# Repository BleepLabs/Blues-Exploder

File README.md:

The Jon Spencer Blues Exploder

Back in 2012 I had the great pleasure of working with Jon Spencer to make this weird thing.
http://bleeplabs.com/exploder/

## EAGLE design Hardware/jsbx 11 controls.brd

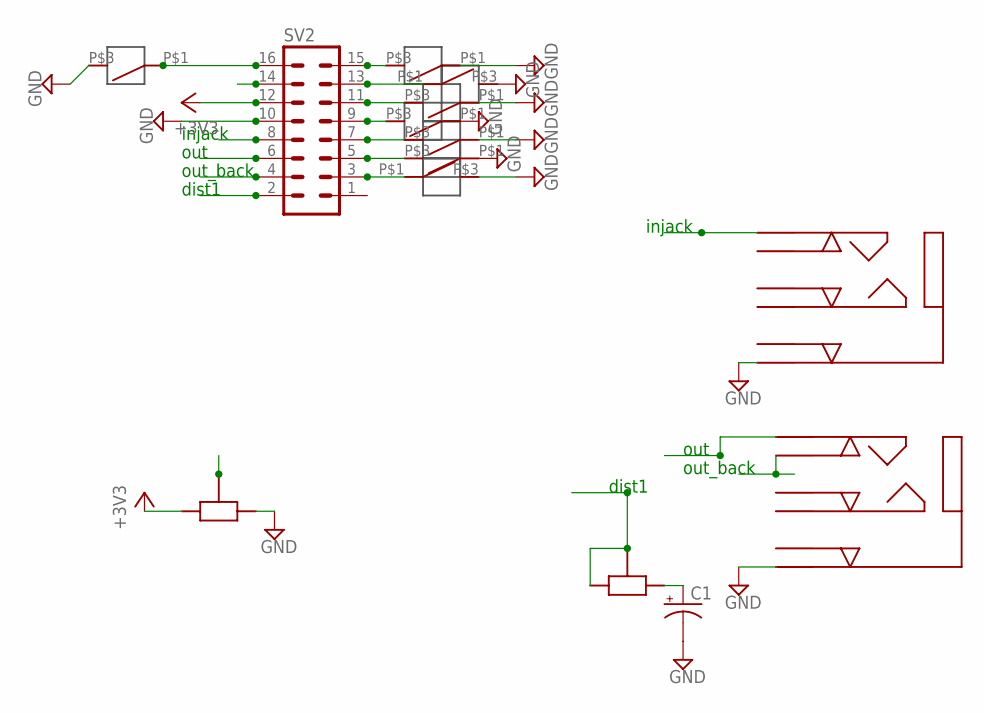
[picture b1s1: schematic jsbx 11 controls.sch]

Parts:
B1, B2, B3, B4, B5, B6, B7, B8: SPDT_TOPHAT
C1: CPOL-USE2.5-7; E2,5-7
SV2: MA08-2
U$12, U$13: POT
U$14, U$15: 1/4STEREO

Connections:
+3V3: SV2.12, U$12.P$1
B1: SV2.14, U$12.P$2
DIST1: SV2.2, U$13.P$1, U$13.P$2
GND: B1.P$1, B1.P$2, B2.P$3, B2.P$4, B3.P$1, B3.P$2, B4.P$1, B4.P$2, B5.P$3, B5.P$4, B6.P$1, B6.P$2, B7.P$1, B7.P$2, B8.P$3, B8.P$4, C1.-, SV2.10, U$12.P$3, U$14.P$1, U$15.P$1
GPOT: B4.P$3, B4.P$4, SV2.9
IN_JACK: SV2.8, U$14.P$3
unnamed: C1.+, U$13.P$3
unnamed: B3.P$3, B3.P$4, SV2.11
unnamed: B2.P$1, B2.P$2, SV2.13
unnamed: B1.P$3, B1.P$4, SV2.15
unnamed: B5.P$1, B5.P$2, SV2.16
unnamed: B6.P$3, B6.P$4, SV2.7
unnamed: B7.P$3, B7.P$4, SV2.5
unnamed: B8.P$1, B8.P$2, SV2.3
OUT: SV2.6, U$15.P$3
OUT_BACK: SV2.4, U$15.P$6
S$1: U$14.P$6

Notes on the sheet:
dist1
injack
out
out_back

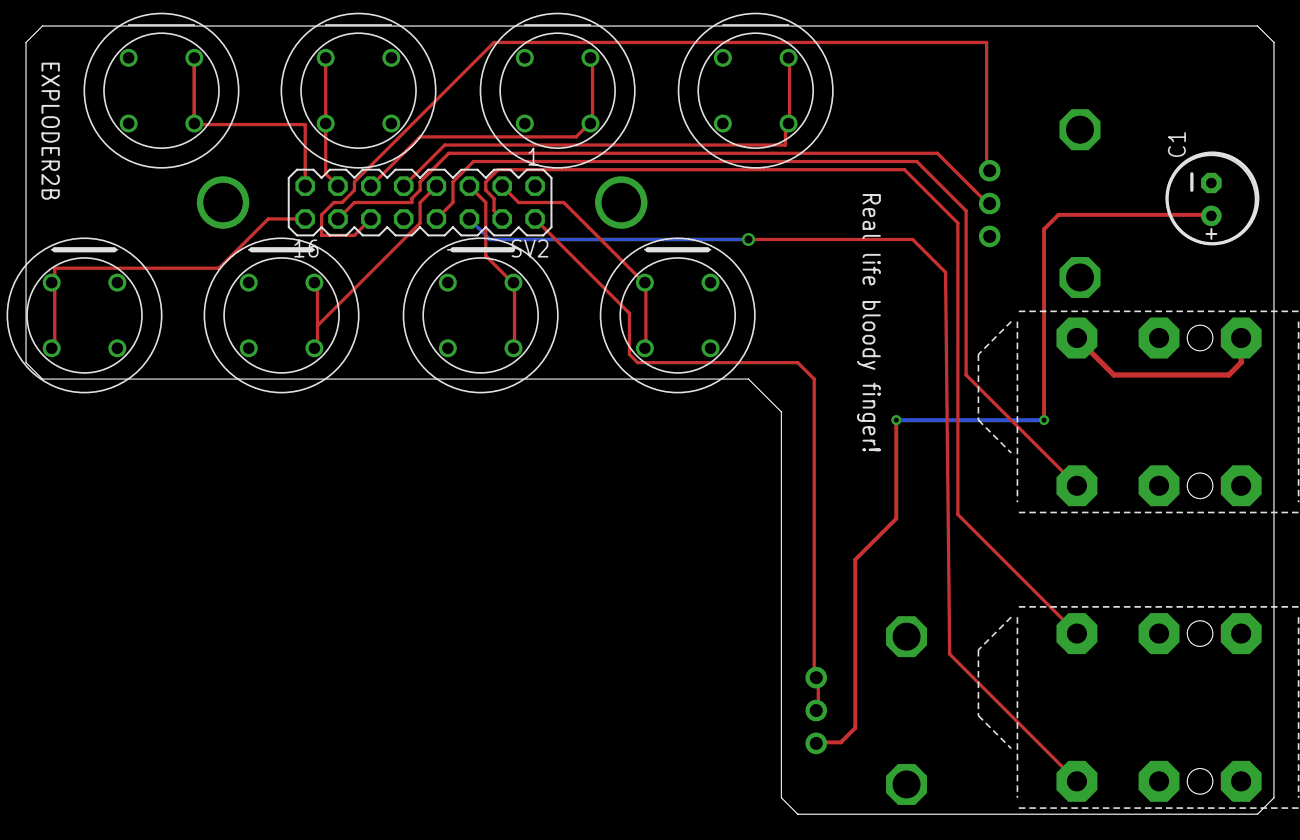
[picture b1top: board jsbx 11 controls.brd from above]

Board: 2 copper layers, 96.5 x 61.0 mm, 14 parts (0 on the bottom side), 16 nets.

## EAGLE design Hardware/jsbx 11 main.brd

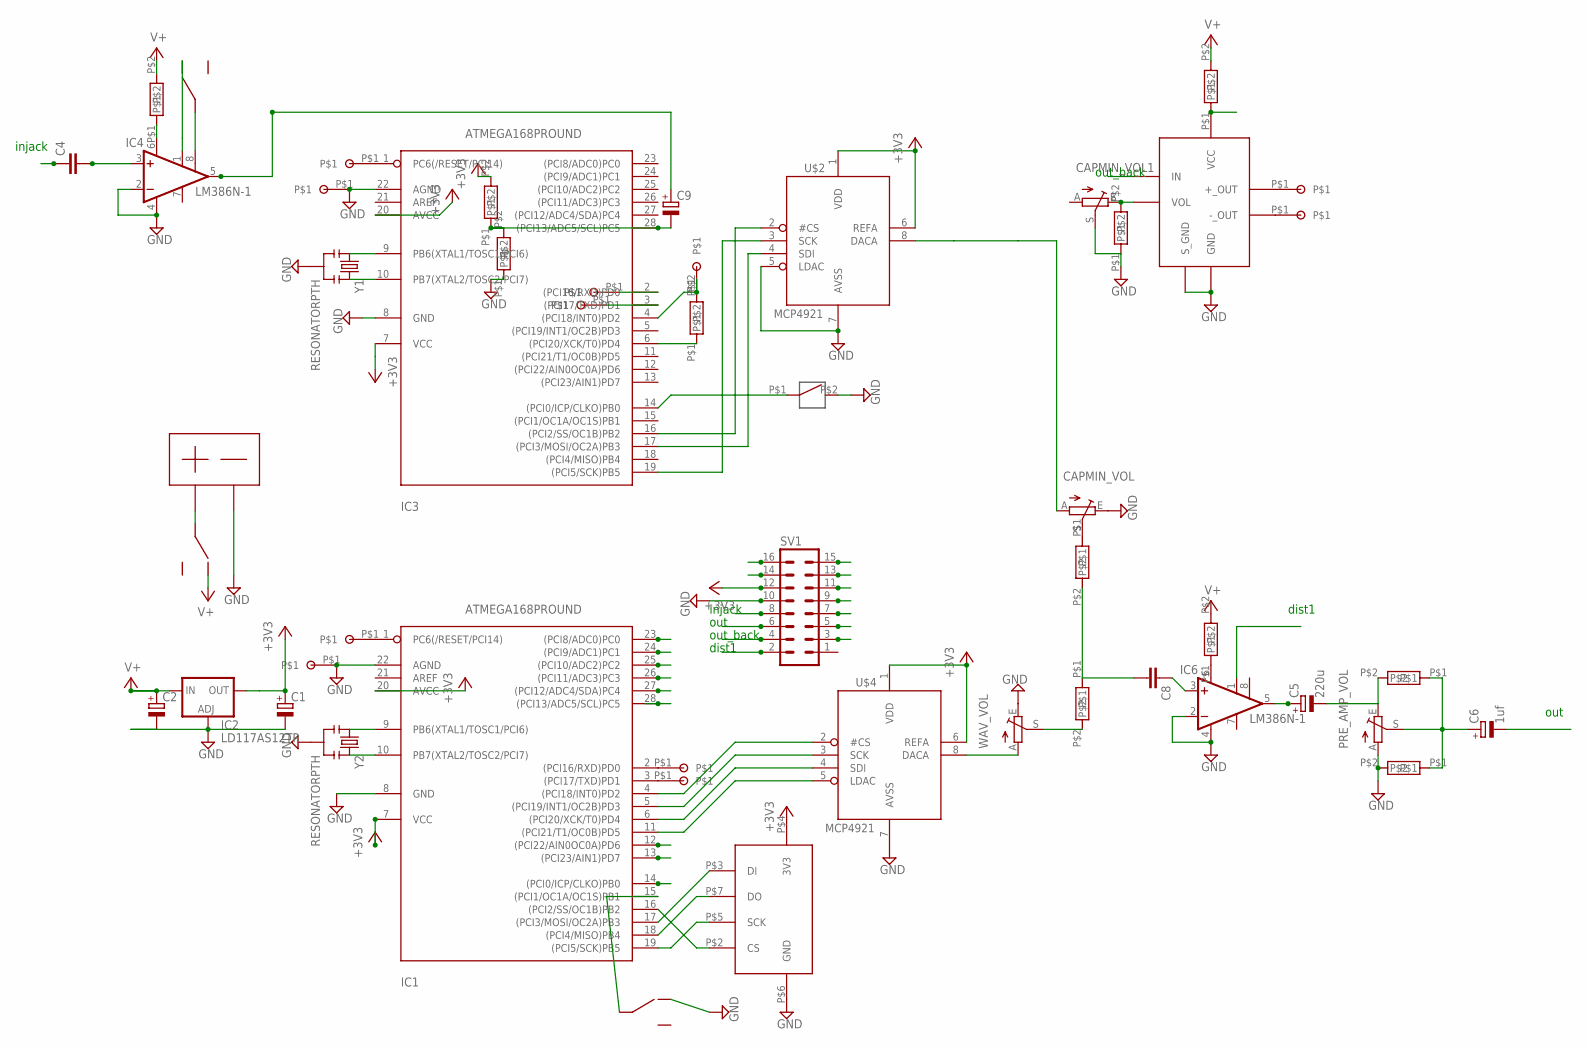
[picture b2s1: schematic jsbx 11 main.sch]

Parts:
C1, C2, C9: CPOL-EUE2-5; E2-5
C4, C8: C-EU025-030X050; C025-030X050
C5: 220u; E2-5
C6: 1uf; E2-5
CAPMIN_VOL, CAPMIN_VOL1: TRIM_EU-CA9H; CA9H
IC1, IC3: ATMEGA168PROUND; DIL28-3-ROUND
IC2: LD117AS12TR; SOT223
IC4, IC6: LM386N-1; DIL08
PRE_AMP_VOL: TRIM_EU-CA9H; CA9H
R1, R2, R4_DIS_386_+, R5, R6, R7, R8, R12-DIS_386_+1, R13-7052+: RESISTOR_PERP
R3: in_386_+; RESISTOR_PERP
R4: 10K; RESISTOR_PERP
SV1: MA08-2
U$1: SD_MICRO_PERP
U$2, U$4: MCP4921; DIL08
U$3: TDA7052; DIP8
U$5, U$16, U$17: SLIDE_HORIZ_OS
U$6: 12MM_TAC_HORIZ
U$7, U$8, U$9, U$10, U$11, U$12, U$13, U$14, U$15, U$22, U$23: PADSMALL
U$18: 9V
WAV_VOL: TRIM_EU-CA9H; CA9H
Y1, Y2: RESONATORPTH; RESONATOR-PTH

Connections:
+3V3: C1.+, IC1.7 (VCC), IC1.20 (AVCC), IC2.4 (OUT), IC3.7 (VCC), IC3.20 (AVCC), R2.P$2, SV1.12, U$1.P$4 (3V3), U$2.1 (VDD), U$2.6 (REFA), U$4.1 (VDD), U$4.6 (REFA)
B1: IC1.28 ((PCI13/ADC5/SCL)PC5), SV1.14
DIST1: IC6.1 (GAIN), SV1.2
GND: C1.-, C2.-, CAPMIN_VOL.E, CAPMIN_VOL1.S, IC1.8 (GND), IC1.22 (AGND), IC2.1 (ADJ), IC3.8 (GND), IC3.22 (AGND), IC4.2 (-IN), IC4.4 (GND), IC6.2 (-IN), IC6.4 (GND), PRE_AMP_VOL.A, R1.P$1, R6.P$2, R12-DIS_386_+1.P$1, SV1.10, U$1.P$6 (GND), U$2.5 (LDAC), U$2.7 (AVSS), U$3.P$3 (S_GND), U$3.P$6 (GND), U$4.7 (AVSS), U$6.P$2, U$11.P$1, U$13.P$1, U$16.P$2, U$18.P$2, WAV_VOL.E, Y1.2, Y2.2
GPOT: IC1.23 ((PCI8/ADC0)PC0), SV1.9
IN_JACK: C4.1, SV1.8
unnamed: IC1.10 (PB7(XTAL2/TOSC2/PCI7)), Y2.3
unnamed: IC1.9 (PB6(XTAL1/TOSC1/PCI6)), Y2.1
unnamed: IC3.10 (PB7(XTAL2/TOSC2/PCI7)), Y1.3
unnamed: IC3.9 (PB6(XTAL1/TOSC1/PCI6)), Y1.1
unnamed: IC1.18 ((PCI4/MISO)PB4), U$1.P$7 (DO)
unnamed: IC1.17 ((PCI3/MOSI/OC2A)PB3), U$1.P$3 (DI)
unnamed: IC1.19 ((PCI5/SCK)PB5), U$1.P$5 (SCK)
unnamed: IC1.16 ((PCI2/SS/OC1B)PB2), U$1.P$2 (CS)
unnamed: IC1.15 ((PCI1/OC1A/OC1S)PB1), U$16.P$1
unnamed: IC1.4 ((PCI18/INT0)PD2), U$4.2 (#CS)
unnamed: IC1.5 ((PCI19/INT1/OC2B)PD3), U$4.3 (SCK)
unnamed: IC1.6 ((PCI20/XCK/T0)PD4), U$4.4 (SDI)
unnamed: IC1.11 ((PCI21/T1/OC0B)PD5), U$4.5 (LDAC)
unnamed: C8.1, IC6.3 (+IN)
unnamed: R8.P$2, WAV_VOL.S
unnamed: IC4.6 (VS), R3.P$1
unnamed: IC1.2 ((PCI16/RXD)PD0), U$14.P$1
unnamed: IC1.24 ((PCI9/ADC1)PC1), SV1.11
unnamed: IC1.25 ((PCI10/ADC2)PC2), SV1.13
unnamed: IC1.26 ((PCI11/ADC3)PC3), SV1.15
unnamed: R13-7052+.P$1, U$3.P$1 (VCC)
unnamed: CAPMIN_VOL1.E, R12-DIS_386_+1.P$2, U$3.P$4 (VOL)
unnamed: C9.-, IC3.28 ((PCI13/ADC5/SCL)PC5), R1.P$2, R2.P$1
unnamed: IC1.27 ((PCI12/ADC4/SDA)PC4), SV1.16
unnamed: IC1.12 ((PCI22/AIN0OC0A)PD6), SV1.7
unnamed: IC1.13 ((PCI23/AIN1)PD7), SV1.5
unnamed: C4.2, IC4.3 (+IN)
unnamed: U$3.P$8 (-_OUT), U$22.P$1
unnamed: C8.2, R4.P$2, R8.P$1
unnamed: IC4.1 (GAIN), U$5.P$2
unnamed: U$17.P$1, U$18.P$1
unnamed: IC1.14 ((PCI0/ICP/CLKO)PB0), SV1.3
unnamed: C5.-, PRE_AMP_VOL.E, R5.P$2
unnamed: IC3.16 ((PCI2/SS/OC1B)PB2), U$2.2 (#CS)
unnamed: IC3.17 ((PCI3/MOSI/OC2A)PB3), U$2.4 (SDI)
unnamed: IC3.19 ((PCI5/SCK)PB5), U$2.3 (SCK)
unnamed: IC6.6 (VS), R4_DIS_386_+.P$1
unnamed: C5.+, IC6.5 (OUT)
unnamed: IC3.14 ((PCI0/ICP/CLKO)PB0), U$6.P$1
unnamed: C9.+, IC4.5 (OUT)
unnamed: CAPMIN_VOL.A, U$2.8 (DACA)
unnamed: IC3.1 (PC6(/RESET/PCI14)), U$8.P$1
unnamed: IC3.2 ((PCI16/RXD)PD0), U$9.P$1
unnamed: IC3.3 ((PCI17/TXD)PD1), U$10.P$1
unnamed: IC1.1 (PC6(/RESET/PCI14)), U$12.P$1
unnamed: IC1.3 ((PCI17/TXD)PD1), U$15.P$1
unnamed: IC3.4 ((PCI18/INT0)PD2), R7.P$2, U$7.P$1
unnamed: IC3.6 ((PCI20/XCK/T0)PD4), R7.P$1
unnamed: U$3.P$5 (+_OUT), U$23.P$1
unnamed: IC4.8 (GAIN), U$5.P$1
unnamed: U$4.8 (DACA), WAV_VOL.A
unnamed: C6.+, PRE_AMP_VOL.S, R5.P$1, R6.P$1
unnamed: CAPMIN_VOL.S, R4.P$1
OUT: C6.-, SV1.6
OUT_BACK: SV1.4, U$3.P$2 (IN)
V+: C2.+, IC2.3 (IN), R3.P$2, R4_DIS_386_+.P$2, R13-7052+.P$2, U$17.P$2

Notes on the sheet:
injack
out_back
out
dist1

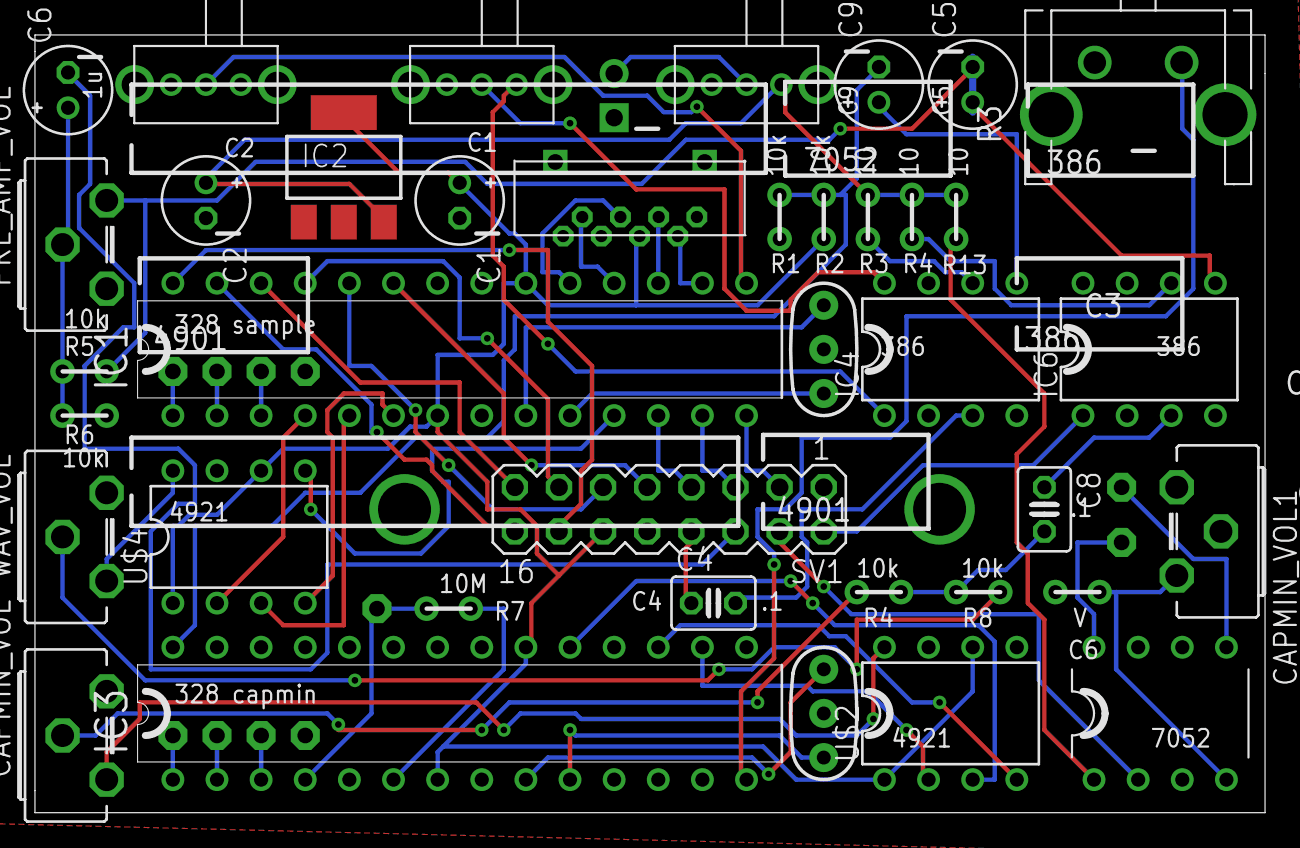
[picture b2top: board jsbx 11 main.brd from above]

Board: 2 copper layers, 70.8 x 44.8 mm, 50 parts (0 on the bottom side), 62 nets.

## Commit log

2016-01-17 :boom::camel: Added .gitattributes & .gitignore files

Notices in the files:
parts and their libraries:
SparkFun-FreqCtrl: Licensing: CC v3.0 Share-Alike You are welcome to use this library for commercial purposes.
